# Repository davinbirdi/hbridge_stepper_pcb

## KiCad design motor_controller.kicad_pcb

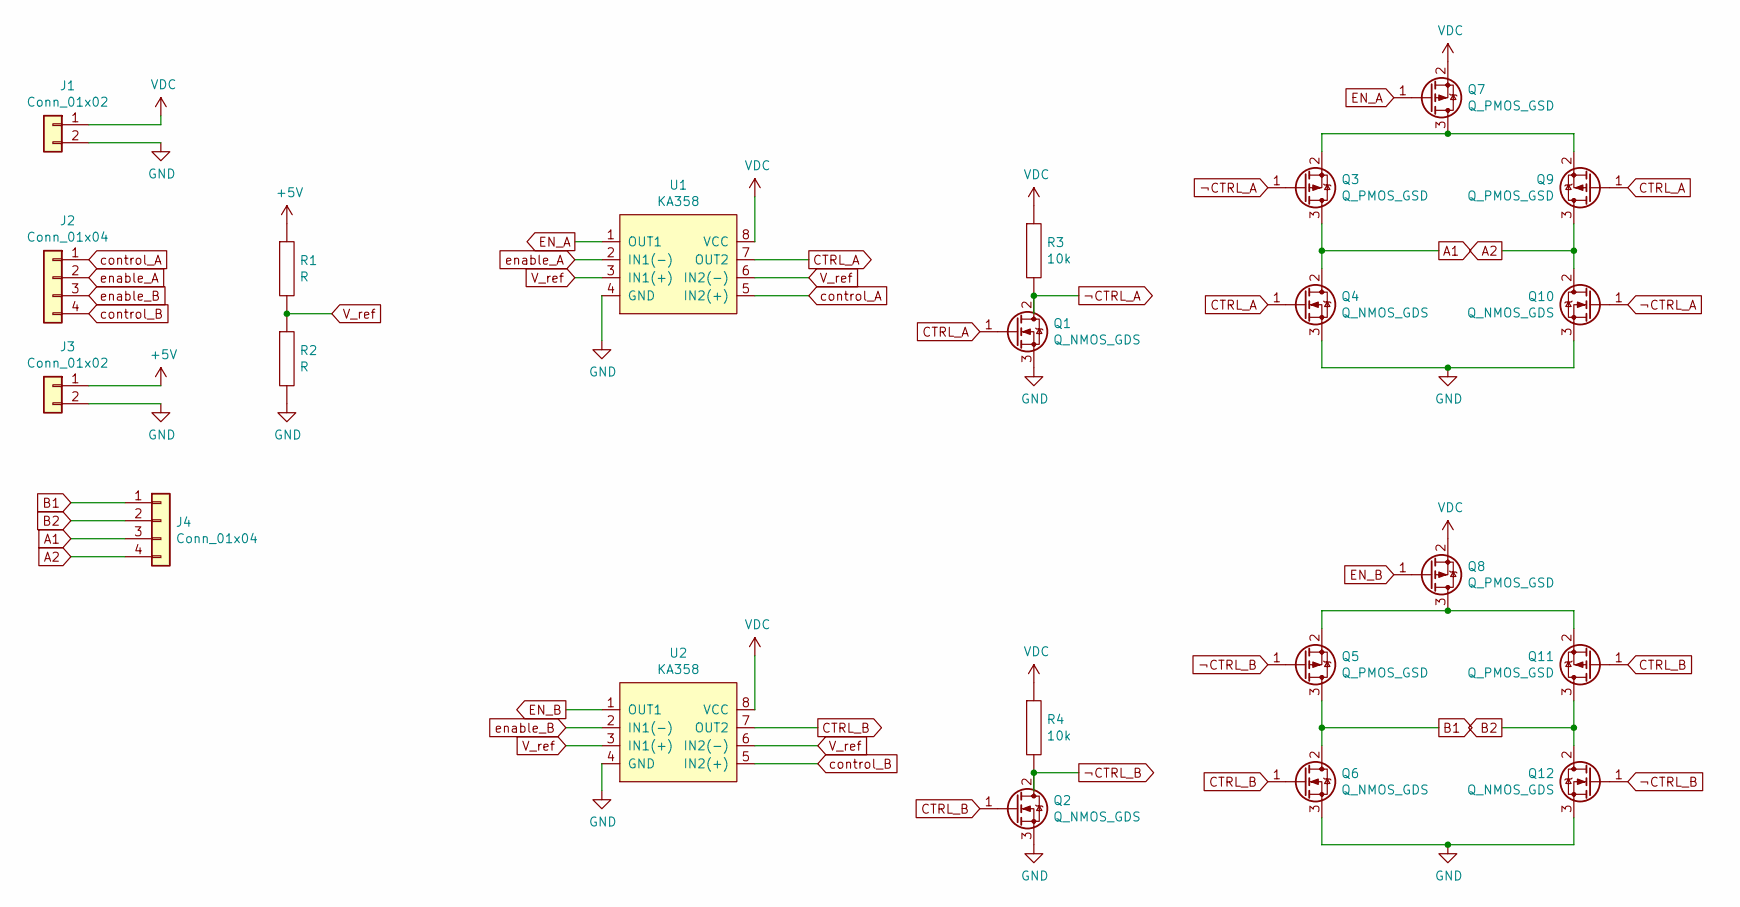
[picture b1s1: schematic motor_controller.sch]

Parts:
J1, J3: Conn_01x02; PinSocket_1x02_P2.54mm_Horizontal
J2, J4: Conn_01x04; PinSocket_1x04_P2.54mm_Horizontal
Q1, Q2: Q_NMOS_GDS; TO-251-3_Vertical
Q3, Q5, Q7, Q8, Q9, Q11: Q_PMOS_GSD; TO-220-3_Horizontal_TabDown
Q4, Q6, Q10, Q12: Q_NMOS_GDS; TO-220-3_Horizontal_TabDown
R1, R2: R; R_Box_L8.4mm_W2.5mm_P5.08mm
R3, R4: 10k; R_Box_L8.4mm_W2.5mm_P5.08mm
U1, U2: KA358; DIP-8_W7.62mm_LongPads

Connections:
+5V: J3.1, R1.1
A1: J4.3, Q3.3 (D), Q4.2 (D)
A2: J4.4, Q9.3 (D), Q10.2 (D)
B1: J4.1, Q5.3 (D), Q6.2 (D)
B2: J4.2, Q11.3 (D), Q12.2 (D)
CTRL_A: Q1.1 (G), Q4.1 (G), Q9.1 (G), U1.7 (OUT2)
CTRL_B: Q2.1 (G), Q6.1 (G), Q11.1 (G), U2.7 (OUT2)
EN_A: Q7.1 (G), U1.1 (OUT1)
EN_B: Q8.1 (G), U2.1 (OUT1)
GND: J1.2, J3.2, Q1.3 (S), Q2.3 (S), Q4.3 (S), Q6.3 (S), Q10.3 (S), Q12.3 (S), R2.2, U1.4 (GND), U2.4 (GND)
unnamed: Q3.2 (S), Q7.3 (D), Q9.2 (S)
unnamed: Q5.2 (S), Q8.3 (D), Q11.2 (S)
VDC: J1.1, Q7.2 (S), Q8.2 (S), R3.1, R4.1, U1.8 (VCC), U2.8 (VCC)
V_ref: R1.2, R2.1, U1.3 (IN1(+)), U1.6 (IN2(-)), U2.3 (IN1(+)), U2.6 (IN2(-))
control_A: J2.1, U1.5 (IN2(+))
control_B: J2.4, U2.5 (IN2(+))
enable_A: J2.2, U1.2 (IN1(-))
enable_B: J2.3, U2.2 (IN1(-))
¬CTRL_A: Q1.2 (D), Q3.1 (G), Q10.1 (G), R3.2
¬CTRL_B: Q2.2 (D), Q5.1 (G), Q12.1 (G), R4.2

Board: 2 copper layers, 22 parts (0 on the bottom side), 20 nets, no tracks yet.

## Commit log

2021-03-20 Initial Commit. PCB Layed Out
2021-03-20 Init Layout2
